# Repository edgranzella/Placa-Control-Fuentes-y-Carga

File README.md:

# Placa Control Fuentes y Carga - Hardware y PCB 🚀

Este repositorio contiene el diseño completo de la placa de circuito impreso (PCB) desarrollado en **KiCad 10** para el sistema de **Control de Fuentes y Gestión de Carga de Baterías**.

---

## 📌 Características del Diseño
* **Gestión de Energía:** Monitoreo y conmutación inteligente entre fuentes de alimentación principales y sistemas de respaldo por batería.
* **Etapa de Carga Integrada:** Circuito de control dedicado para la recarga segura, regulación de corriente y protección térmica del banco de baterías.
* **Supervisión Analógica:** Divisores de tensión de precisión y sensores de corriente dispuestos para la telemetría de voltajes críticos.
* **Protección de Entrada:** Fusibles rearmables, diodos de protección contra inversión de polaridad y supresores de transitorios (TVS).

---

## 🛠️ Especificaciones Técnicas de Fabricación
Configuración sugerida basada en las reglas de diseño (DRC) aplicadas en KiCad 10:

| Parámetro | Configuración Sugerida |
| :--- | :--- |
| **Capas (Layers)** | 2 Capas |
| **Grosor de la Placa** | 1.6 mm |
| **Grosor del Cobre** | 1 oz / 2 oz (Recomendado para pistas de alta corriente en etapas de carga) |
| **Acabado Superficial** | HASL (with lead) o ENIG |

---

## 👥 Desarrollado por
* **Damian Granzella** - *Ingeniería de Hardware* - [edgranzella](https://github.com)

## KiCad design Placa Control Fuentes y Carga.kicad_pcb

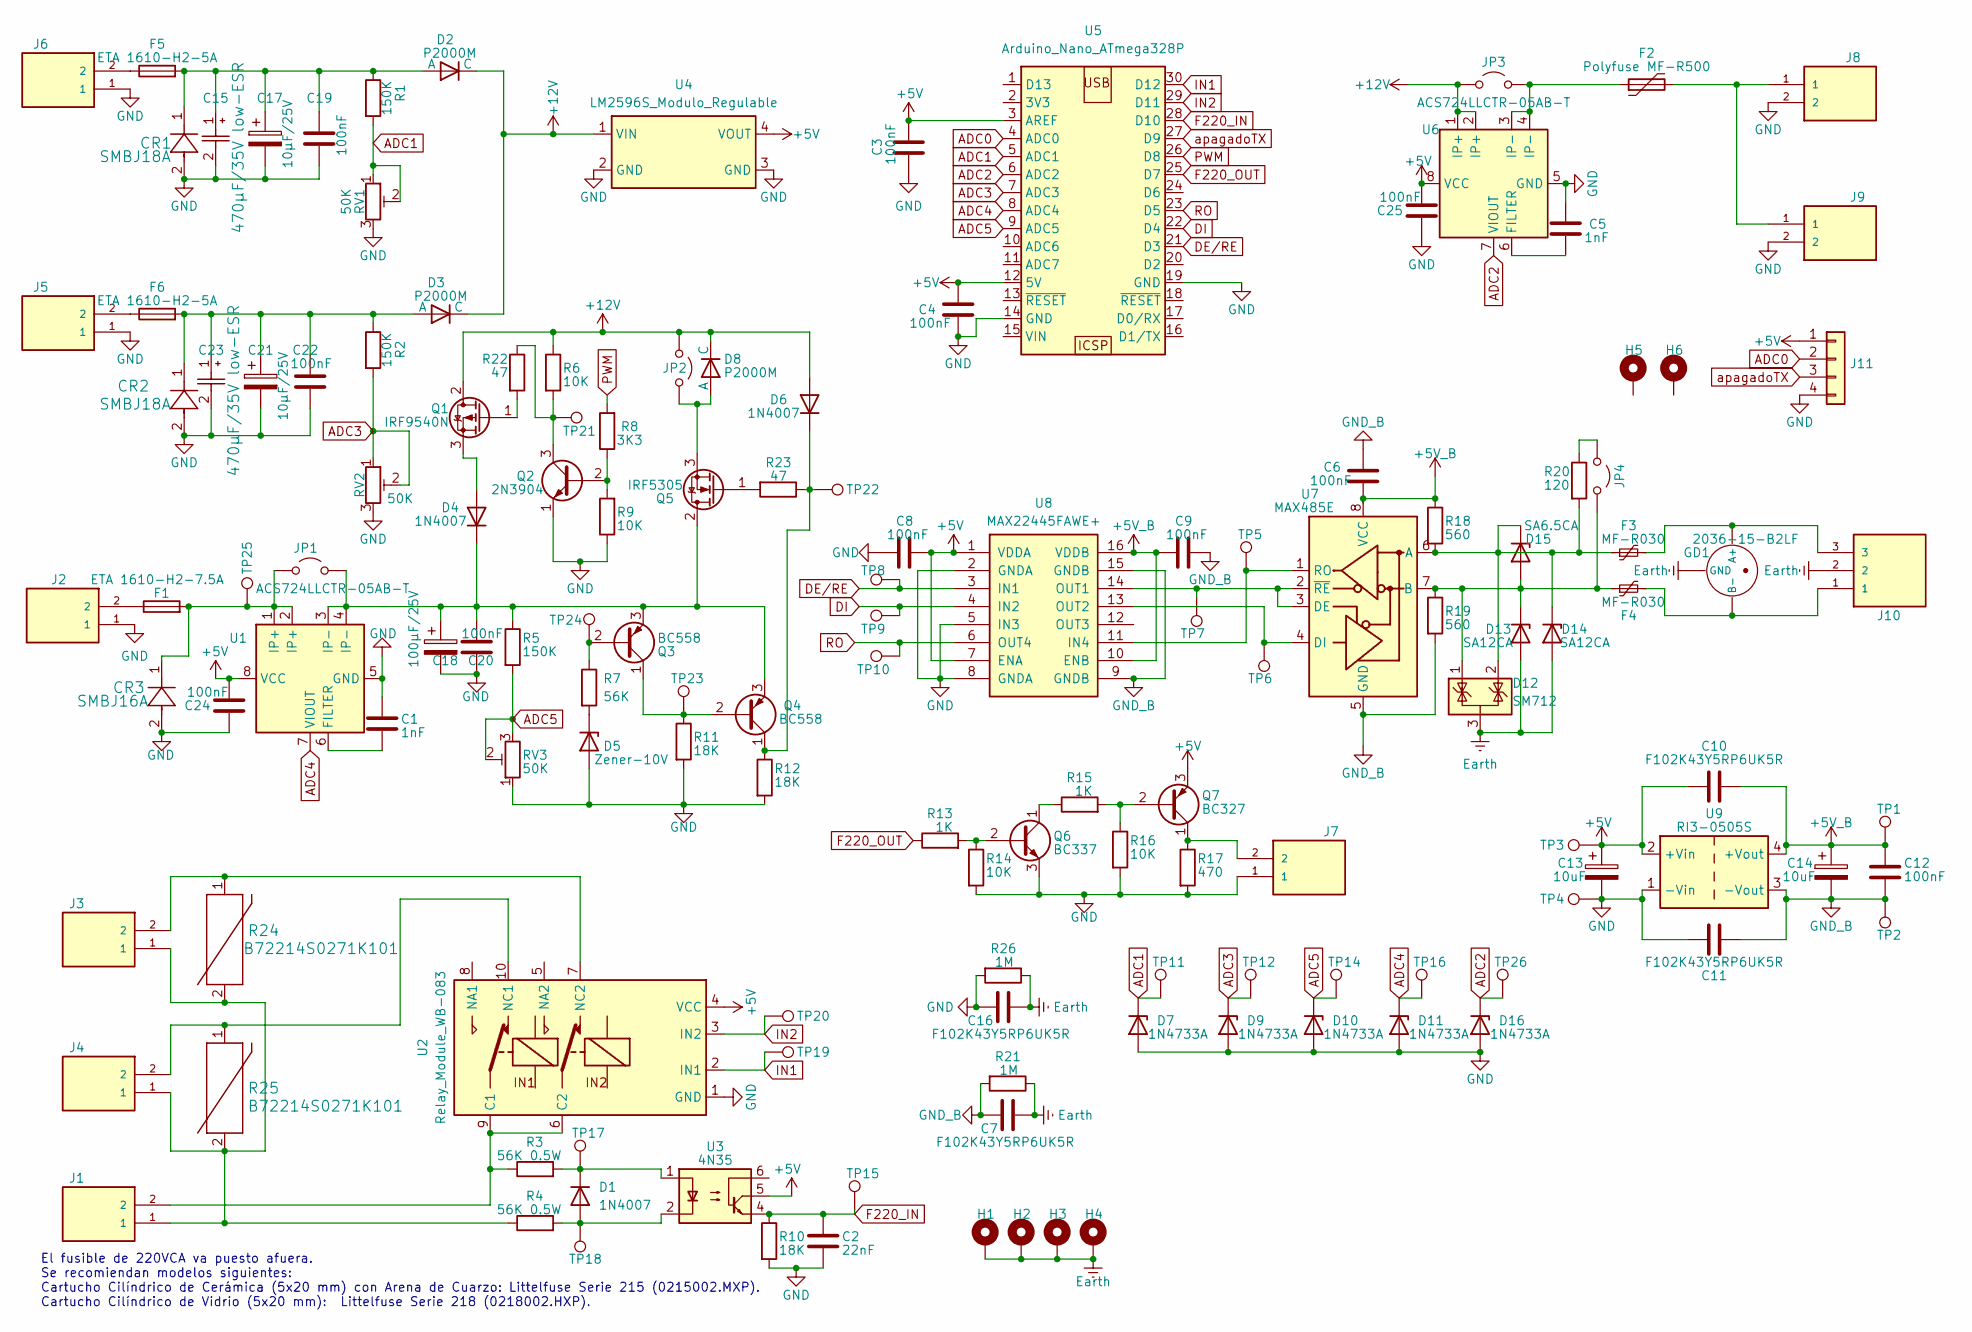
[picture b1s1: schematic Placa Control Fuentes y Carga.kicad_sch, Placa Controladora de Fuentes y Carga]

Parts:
C1, C5: 1nF; C_Disc_D5.0mm_W2.5mm_P2.50mm
C2: 22nF; C_Disc_D5.0mm_W2.5mm_P2.50mm
C3, C4, C6, C8, C9, C12, C19, C20, C22, C24, C25: 100nF; C_Disc_D5.0mm_W2.5mm_P2.50mm
C7, C10, C11, C16: F102K43Y5RP6UK5R; CAP_F_11X5P_VIS
C13, C14: 10uF; CP_Radial_D5.0mm_P2.00mm
C15, C23: 470µF/35V low-ESR; CAP_UAQ_10X20_NCH
C17, C21: 10µF/25V; CP_Radial_D5.0mm_P2.00mm
C18: 100µF/25V; CP_Radial_D5.0mm_P2.00mm
CR1, CR2: SMBJ18A; DIODE_DO214AA
CR3: SMBJ16A; DIODE_DO214AA
D1, D4, D6: 1N4007; D_DO-41_SOD81_P10.16mm_Horizontal
D2, D3, D8: P2000M; D_P600_R-6_P15.24mm_Horizontal
D5: Zener-10V; D_DO-35_SOD27_P7.62mm_Horizontal
D7, D9, D10, D11, D16: 1N4733A; D_DO-41_SOD81_P10.16mm_Horizontal
D12: SM712; SOT-23_Handsoldering
D13, D14: SA12CA; DO-204AC_SA
D15: SA6.5CA; DO-204AC_SA
F1: ETA 1610-H2-7.5A; FuseHolder_Blade_ATO_Littelfuse_FLR_178.6165
F2: Polyfuse MF-R500; FUSE_MF-R500_BRN
F3, F4: MF-R030; Fuse_Bourns_MF-RHT050
F5, F6: ETA 1610-H2-5A; FuseHolder_Blade_ATO_Littelfuse_FLR_178.6165
GD1: 2036-15-B2LF; GDT_Yageo_3RxxxxL-6
H1, H2, H3, H4, H5, H6: MountingHole_Pad; MountingHole_3.2mm_M3_Pad
J1, J2, J3, J4, J5, J6, J7, J8, J9: TBP01R1-508-02BE; TerminalBlock_Phoenix_MKDS-1,5-2-5.08_1x02_P5.08mm_Horizont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
J10: TBP01R1-508-03BE; TerminalBlock_Phoenix_MKDS-1,5-2-5.08_1x03_P5.08mm_Horizont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
J11: Conn_01x04; PinHeader_1x04_P2.54mm_Vertical
JP1, JP2, JP3, JP4: Jumper_2_Open; PinHeader_1x02_P2.54mm_Vertical
Q1: IRF9540N; TO-220-3_Vertical
Q2: 2N3904; TO-92_Inline
Q3, Q4: BC558; TO-92_HandSolder
Q5: IRF5305; TO-220-3_Vertical
Q6: BC337; TO-92_HandSolder
Q7: BC327; TO-92_HandSolder
R1, R2, R5: 150K; R_Axial_DIN0207_L6.3mm_D2.5mm_P7.62mm_Horizontal
R3, R4: 56K 0.5W; R_Axial_DIN0309_L9.0mm_D3.2mm_P12.70mm_Horizontal
R6, R9, R14, R16: 10K; R_Axial_DIN0207_L6.3mm_D2.5mm_P7.62mm_Horizontal
R7: 56K; R_Axial_DIN0207_L6.3mm_D2.5mm_P7.62mm_Horizontal
R8: 3K3; R_Axial_DIN0207_L6.3mm_D2.5mm_P7.62mm_Horizontal
R10, R11, R12: 18K; R_Axial_DIN0207_L6.3mm_D2.5mm_P7.62mm_Horizontal
R13, R15: 1K; R_Axial_DIN0207_L6.3mm_D2.5mm_P7.62mm_Horizontal
R17: 470; R_Axial_DIN0207_L6.3mm_D2.5mm_P7.62mm_Horizontal
R18, R19: 560; R_Axial_DIN0207_L6.3mm_D2.5mm_P7.62mm_Horizontal
R20: 120; R_Axial_DIN0207_L6.3mm_D2.5mm_P7.62mm_Horizontal
R21, R26: 1M; R_Axial_DIN0207_L6.3mm_D2.5mm_P7.62mm_Horizontal
R22, R23: 47; R_Axial_DIN0207_L6.3mm_D2.5mm_P7.62mm_Horizontal
R24, R25: B72214S0271K101; VARS_B72214S0271K101_TDK
RV1, RV2, RV3: 50K; Potentiometer_Bourns_3296W_Vertical
TP1, TP2, TP3, TP4, TP5, TP6, TP7, TP8, TP9, TP10, TP11, TP12, TP14, TP15, TP16, TP17, TP18, TP19, TP20, TP21, TP22, TP23, TP24, TP25, TP26: TestPoint; TestPoint_THTPad_D2.5mm_Drill1.2mm
U1, U6: ACS724LLCTR-05AB-T; SOIC-8_3.9x4.9mm_P1.27mm
U2: Relay_Module_WB-083
U3: 4N35; DIP-6_W7.62mm
U4: LM2596S_Modulo_Regulable; Modulo Step Down Regulable LM2596
U5: Arduino_Nano_ATmega328P; Arduino_Nano
U7: MAX485E; SOIC-8_3.9x4.9mm_P1.27mm
U8: MAX22445FAWE+; SOIC-16W_7.5x10.3mm_P1.27mm
U9: RI3-0505S; CONV_RI3-0505S

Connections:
+5V: C3.1, C4.1, C8.1, C10.2, C13.1, C24.2, C25.2, J11.1, Q7.3 (E), TP3.1 (1_1), U1.8 (VCC), U2.4 (VCC), U3.5, U4.4 (VOUT), U5.3 (AREF), U5.12 (5V), U6.8 (VCC), U8.1 (VDDA), U8.7 (ENA), U9.2 (+Vin)
+5V_B: C6.2, C9.2, C10.1, C12.1, C14.1, R18.1, TP1.1 (1_1), U7.8 (VCC), U8.10 (ENB), U8.16 (VDDB), U9.4 (+Vout)
+12V: D2.1 (C), D3.1 (C), D6.2 (A), D8.1 (C), JP2.1 (A), JP3.1 (A), Q1.2 (D), R6.1, U4.1 (VIN), U6.1 (IP+), U6.2 (IP+)
ADC0: J11.2, U5.4 (ADC0)
ADC1: D7.1 (K), R1.2, RV1.1, RV1.2, TP11.1 (1_1), U5.5 (ADC1)
ADC2: D16.1 (K), TP26.1 (1_1), U5.6 (ADC2), U6.7 (VIOUT)
ADC3: D9.1 (K), R2.2, RV2.1, RV2.2, TP12.1 (1_1), U5.7 (ADC3)
ADC4: D11.1 (K), TP16.1 (1_1), U1.7 (VIOUT), U5.8 (ADC4)
ADC5: D10.1 (K), R5.2, RV3.2, RV3.3, TP14.1 (1_1), U5.9 (ADC5)
DE/RE: TP8.1 (1_1), U5.21 (D3), U8.3 (IN1)
DI: TP9.1 (1_1), U5.22 (D4), U8.4 (IN2)
Earth: C7.2, C16.2, D12.3 (A), D13.2 (A), D14.2 (A), GD1.2 (GND), H1.1 (1_1), H2.1 (1_1), H3.1 (1_1), H4.1 (1_1), J10.2, R21.1, R26.1
F220_IN: C2.1, R10.1, TP15.1 (1_1), U3.4, U5.28 (D10)
F220_OUT: R13.1, U5.25 (D7)
GND: C1.1, C2.2, C3.2, C4.2, C5.1, C8.2, C11.2, C13.2, C15.2, C16.1, C17.2, C18.2, C19.2, C20.1, C21.2, C22.1, C23.2, C24.1, C25.1, CR1.2, CR2.2, CR3.2, D5.2 (A), D7.2 (A), D9.2 (A), D10.2 (A), D11.2 (A), D16.2 (A), J2.1, J5.1, J6.1, J7.1, J8.2, J9.2, J11.4, Q2.1 (E), Q6.3 (E), R9.1, R10.2, R11.2, R12.2, R14.2, R16.2, R17.2, R26.2, RV1.3, RV2.3, RV3.1, TP4.1 (1_1), U1.5 (GND), U2.1 (GND), U4.2 (GND), U4.3 (GND), U5.14 (GND), U5.19 (GND), U6.5 (GND), U8.2 (GNDA), U8.5 (IN3), U8.8 (GNDA), U9.1 (-Vin)
GND_B: C6.1, C7.1, C9.1, C11.1, C12.2, C14.2, R19.2, R21.2, TP2.1 (1_1), U7.5 (GND), U8.9 (GNDB), U8.15 (GNDB), U9.3 (-Vout)
IN1: TP19.1 (1_1), U2.2 (IN1), U5.30 (D12)
IN2: TP20.1 (1_1), U2.3 (IN2), U5.29 (D11)
unnamed: D1.2 (A), R4.2, TP18.1 (1_1), U3.2
unnamed: D1.1 (K), R3.2, TP17.1 (1_1), U3.1
unnamed: C15.1, C17.1, C19.1, CR1.1, D2.2 (A), F5.2, R1.1
unnamed: C21.1, C22.2, C23.1, CR2.1, D3.2 (A), F6.2, R2.1
unnamed: D4.2 (A), Q1.3 (S)
unnamed: C18.1, C20.2, D4.1 (K), JP1.2 (B), Q3.3 (E), Q4.3 (E), Q5.2 (D), R5.1, U1.3 (IP-), U1.4 (IP-)
unnamed: D5.1 (K), R7.2
unnamed: D6.1 (K), Q4.1 (C), R12.1, R23.1, TP22.1 (1_1)
unnamed: D8.2 (A), JP2.2 (B), Q5.3 (S)
unnamed: D12.1 (K), D13.1 (K), D15.2 (A), F4.1, JP4.2 (B), R19.1, U7.7 (B)
unnamed: D12.2 (K), D14.1 (K), D15.1 (K), F3.1, R18.2, R20.2, U7.6 (A)
unnamed: F1.1, J2.2
unnamed: F2.2, J8.1, J9.1
unnamed: F5.1, J6.2
unnamed: F6.1, J5.2
unnamed: F3.2, GD1.1 (A+), J10.3
unnamed: F4.2, GD1.3 (B-), J10.1
unnamed: J1.1, J3.1, J4.1, R4.1, R24.2, R25.2
unnamed: CR3.1, F1.2, JP1.1 (A), TP25.1 (1_1), U1.1 (IP+), U1.2 (IP+)
unnamed: F2.1, JP3.2 (B), U6.3 (IP-), U6.4 (IP-)
unnamed: JP4.1 (A), R20.1
unnamed: Q1.1 (G), R22.2
unnamed: Q2.2 (B), R8.1, R9.2
unnamed: Q2.3 (C), R6.2, R22.1, TP21.1 (1_1)
unnamed: Q3.2 (B), R7.1, TP24.1 (1_1)
unnamed: Q3.1 (C), Q4.2 (B), R11.1, TP23.1 (1_1)
unnamed: Q5.1 (G), R23.2
unnamed: Q6.2 (B), R13.2, R14.1
unnamed: Q6.1 (C), R15.1
unnamed: Q7.2 (B), R15.2, R16.1
unnamed: J7.2, Q7.1 (C), R17.1
unnamed: C1.2, U1.6 (FILTER)
unnamed: J1.2, R3.1, U2.6 (C2), U2.9 (C1)
unnamed: J4.2, R25.1, U2.10 (NC1)
unnamed: J3.2, R24.1, U2.7 (NC2)
unnamed: C5.2, U6.6 (FILTER)
unnamed: TP7.1 (1_1), U7.2 (~RE), U7.3 (DE), U8.14 (OUT1)
unnamed: TP6.1 (1_1), U7.4 (DI), U8.13 (OUT2)
unnamed: TP5.1 (1_1), U7.1 (RO), U8.11 (IN4)
PWM: R8.2, U5.26 (D8)
RO: TP10.1 (1_1), U5.23 (D5), U8.6 (OUT4)
apagadoTX: J11.3, U5.27 (D9)

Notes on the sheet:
El fusible de 220VCA va puesto afuera. Se recomiendan modelos siguientes: Cartucho Cilíndrico de Cerámica (5x20 mm) con Arena de Cuarzo: Littelfuse Serie 215 (0215002.MXP). Cartucho Cilíndrico de Vidrio (5x20 mm): Littelfuse Serie 218 (0218002.HXP).

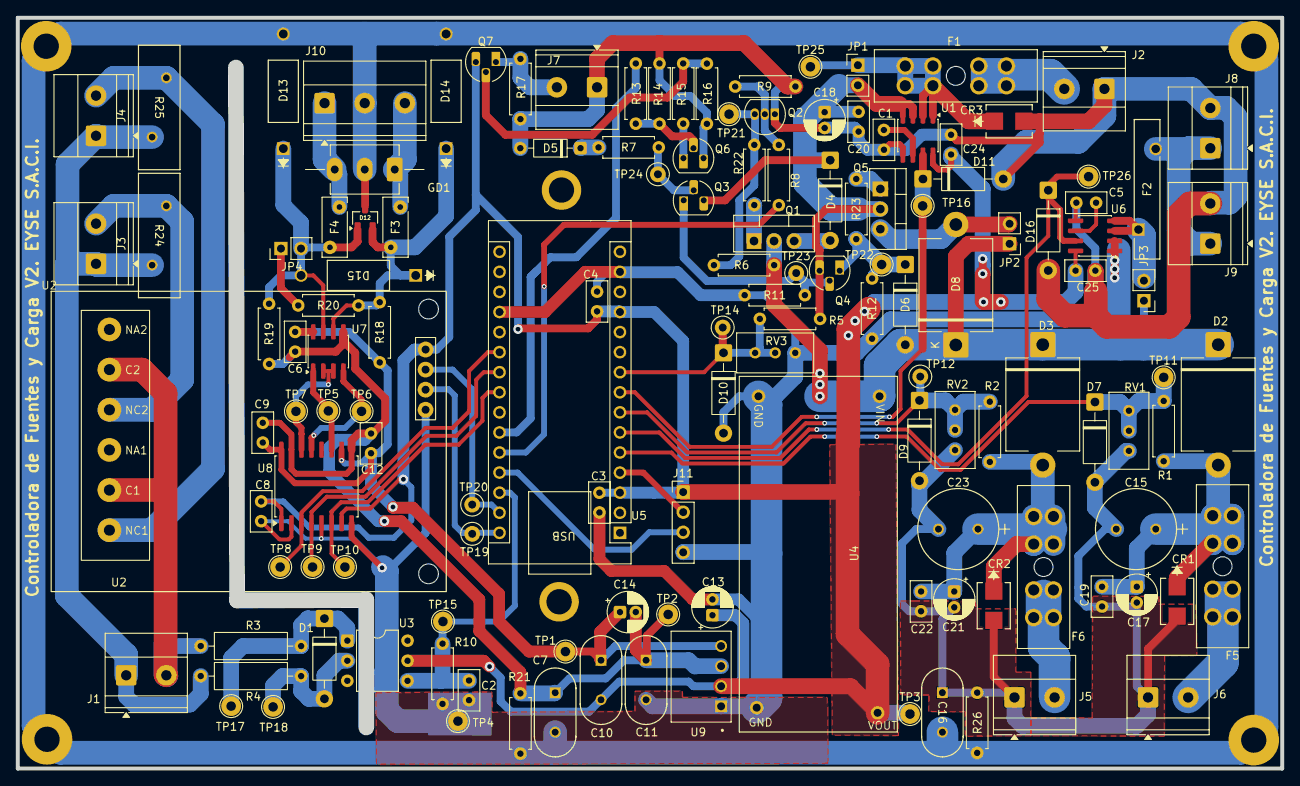
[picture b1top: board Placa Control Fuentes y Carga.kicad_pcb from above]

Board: 2 copper layers, 160.0 x 95.0 mm, 142 parts (0 on the bottom side), 60 nets.
